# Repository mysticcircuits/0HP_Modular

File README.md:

# 0HP_Modular
A collection of small circuit boards meant to save space in a Eurorack modular synthesizer.

However they can be adapted and used in all kinds of scenarios, including other formats.

All of the 0HPs have a video build guide where I walk you through the build in real time.  These modules are ideal for DIY beginners and I wanted to make things easier for beginners to follow along like a Bob Ross video.  For the relevant videos, look at the links below:

0HP 0ttenuator: https://youtu.be/Et-Cd0Tk92Y

0HP Butt0n: https://youtu.be/Q1uErexXjrM

0HP Blinkus: https://youtu.be/KXeKGlNDjDo

0HP OR Gate: https://youtu.be/0qNCt1tknoM

0HP AND Gate: https://youtu.be/TZeJ5ZJfBpM

0HP Vactrol Modules: https://youtu.be/1y4UL7ndCgU

0HP EYEtenuator: https://youtu.be/DLzy-zN2tSA

0HP Filter: https://youtu.be/64bybnugtrU

0HP Envelope: https://youtu.be/DnMquwOY_Zk

If you are new to soldering, here is a guide I made going over the basics: https://www.youtube.com/watch?v=Z_U6xBCo2K4

Please note that these files are shared under the Creative Commons Attribution-NonCommercial 3.0 United States (CC BY-NC 3.0 US) licence, details of which can be found here:

https://creativecommons.org/licenses/by-nc/3.0/us/

This licence prohibits using these designs for commercial use.  Feel free to make circuit boards for yourself but we ask that you not sell them.  If you are interested in purchasing either a circuit board, panel or kit you can go to our website or visit one of our retailers.

http://www.mysticcircuits.com/

https://www.thonk.co.uk/shop/mystic-circuits-0hp-modular-pcbs/

Enjoy the designs <33

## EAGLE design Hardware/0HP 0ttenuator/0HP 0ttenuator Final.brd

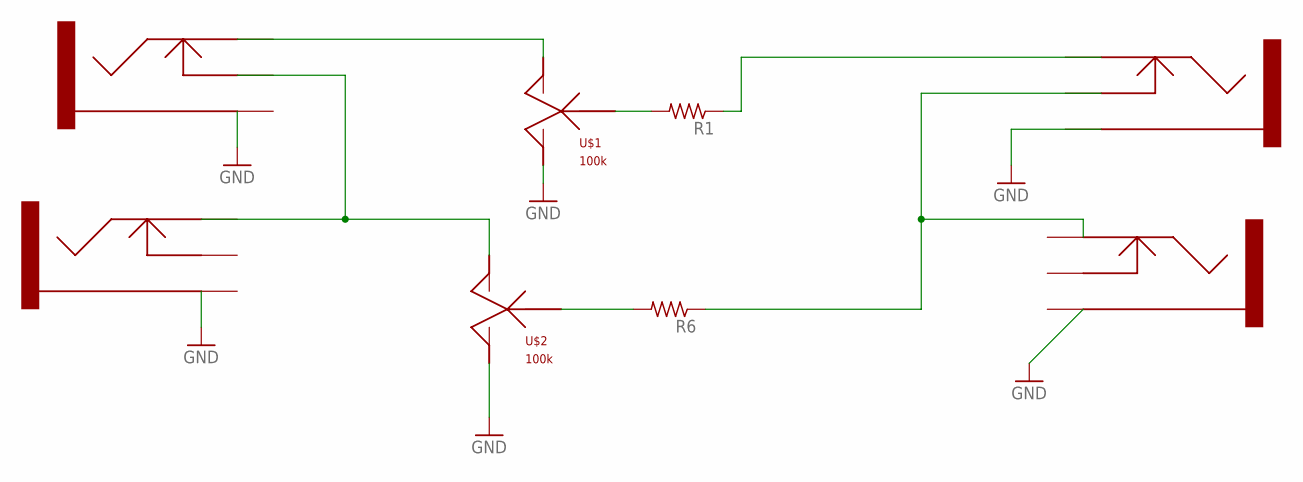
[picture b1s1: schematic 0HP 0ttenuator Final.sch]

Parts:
CV1, CV2: 3.5MMJACK; 3.5MMPHONEJACK
IN: 3.5MMJACK; 3.5MMPHONEJACK
OUT: 3.5MMJACK; 3.5MMPHONEJACK
R1, R6: R-US_0207/10; 0207/10
U$1, U$2: 100k; ALPHAPOT_BOARDMOUNT

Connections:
GND: CV1.SLEEVE, CV2.SLEEVE, IN.SLEEVE, OUT.SLEEVE, U$1.RIGHT, U$2.RIGHT
unnamed: CV2.TIP, U$1.LEFT
unnamed: R1.2, U$1.MID
unnamed: CV1.TIP, CV2.SWITCH, U$2.LEFT
unnamed: OUT.TIP, R1.1
unnamed: IN.TIP, OUT.SWITCH, R6.1
unnamed: R6.2, U$2.MID

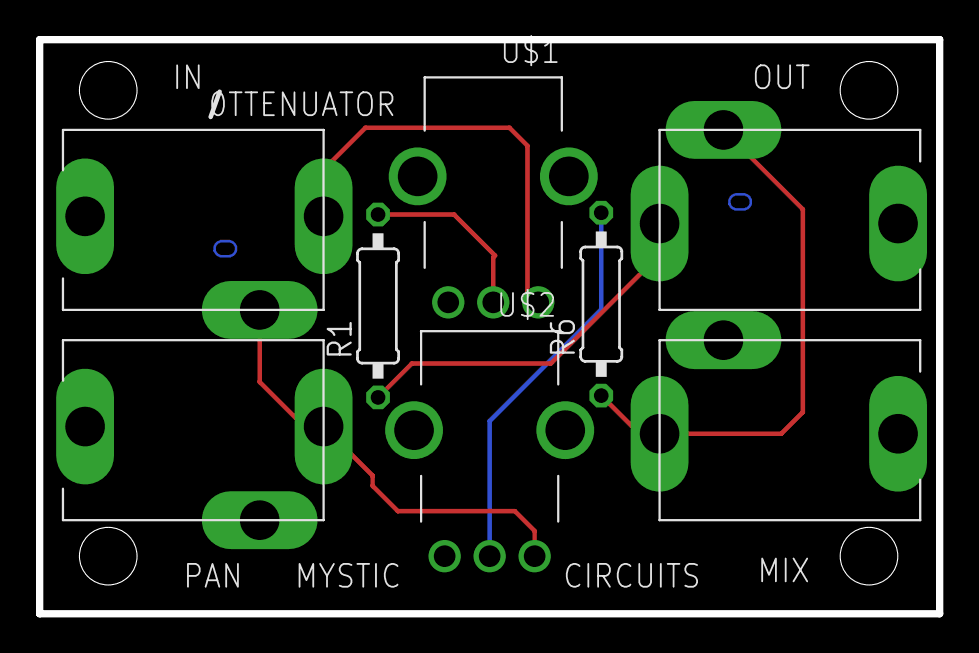
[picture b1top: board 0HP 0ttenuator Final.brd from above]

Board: 2 copper layers, 50.0 x 31.9 mm, 8 parts (0 on the bottom side), 7 nets.

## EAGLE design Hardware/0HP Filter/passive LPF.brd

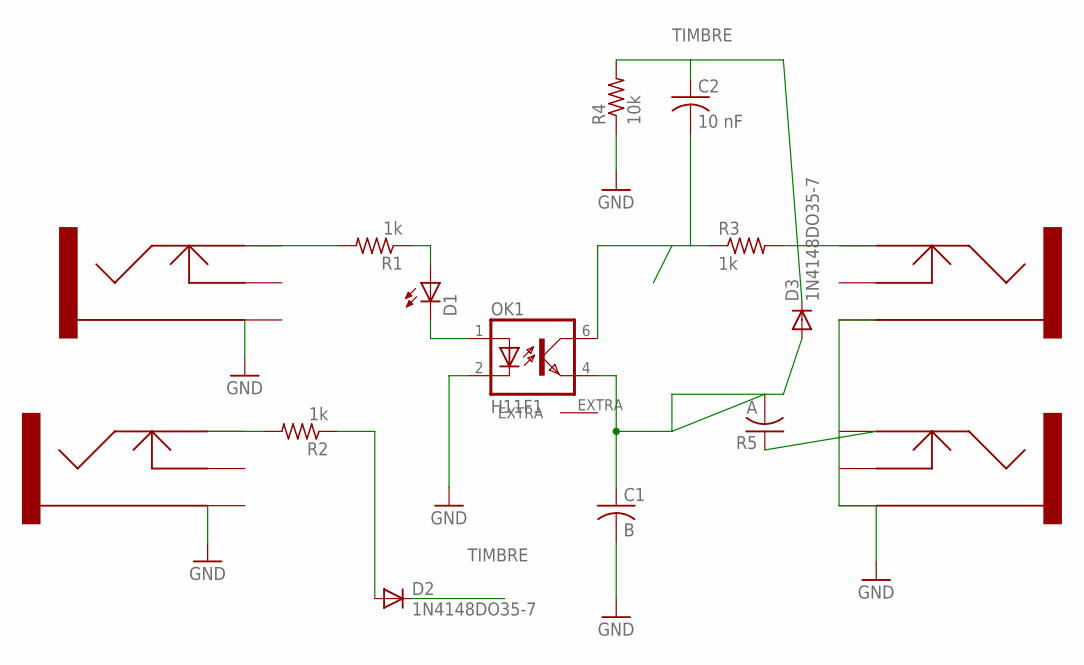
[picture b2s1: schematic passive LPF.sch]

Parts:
C1: B; C050-025X075
C2: 10 nF; C025-024X044
CV1, CV2: 3.5MMJACK; 3.5MMPHONEJACK
D1: LED3MM
D2, D3: 1N4148DO35-7; DO35-7
IN: 3.5MMJACK; 3.5MMPHONEJACK
OK1: H11F1; DIL05
OUT: 3.5MMJACK; 3.5MMPHONEJACK
R1, R2, R3: 1k; 0207/2V
R4: 10k; 0207/2V
R5: A; C050-025X075

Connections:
GND: C1.2, CV1.SLEEVE, CV2.SLEEVE, IN.SLEEVE, OK1.2 (C), OUT.SLEEVE, R4.1
unnamed: CV2.TIP, R1.2
unnamed: D1.A, R1.1
unnamed: D1.K (C), OK1.1 (A)
unnamed: CV1.TIP, R2.2
unnamed: D2.A, R2.1
unnamed: C1.1, D3.A, OK1.4 (EMIT), R5.2
unnamed: C2.2, OK1.6 (COL), R3.1
unnamed: IN.TIP, R5.1
unnamed: OUT.TIP, R3.2
TIMBRE: C2.1, D2.C, D3.C, R4.2

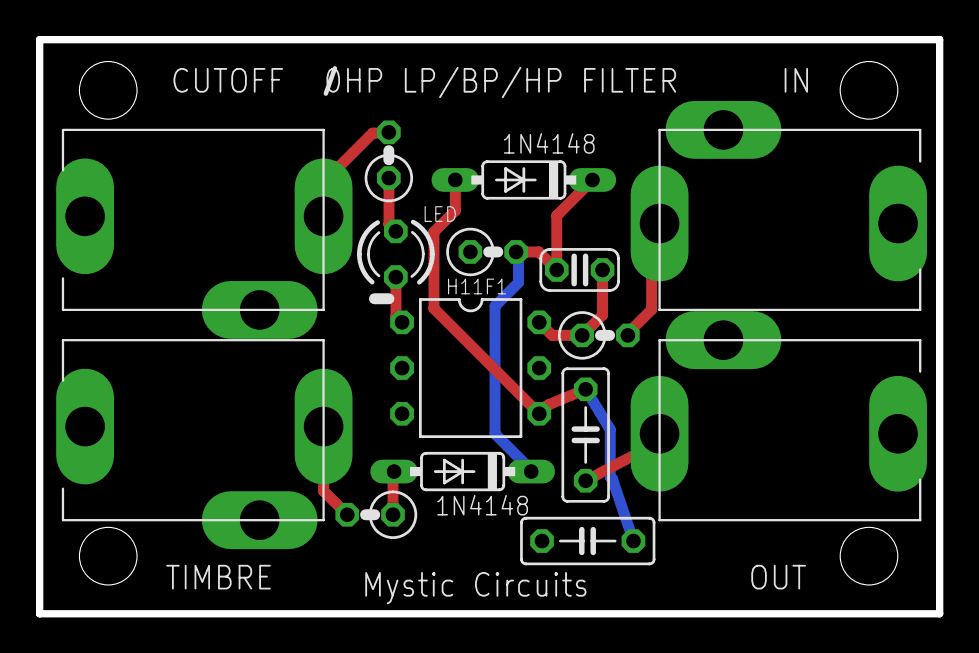
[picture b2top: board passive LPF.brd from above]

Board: 2 copper layers, 50.0 x 31.9 mm, 15 parts (0 on the bottom side), 11 nets.

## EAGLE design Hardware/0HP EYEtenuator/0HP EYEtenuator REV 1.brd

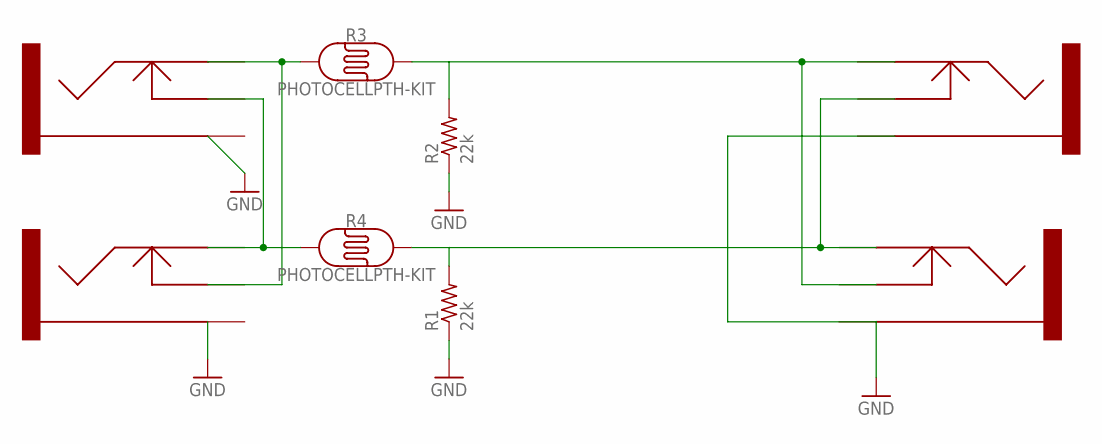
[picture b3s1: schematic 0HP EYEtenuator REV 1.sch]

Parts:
CV1, CV2: 3.5MMJACK; 3.5MMPHONEJACK
IN: 3.5MMJACK; 3.5MMPHONEJACK
OUT: 3.5MMJACK; 3.5MMPHONEJACK
R1, R2: 22k; 0207/2V
R3, R4: PHOTOCELLPTH-KIT; PHOTOCELL-KIT

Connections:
GND: CV1.SLEEVE, CV2.SLEEVE, IN.SLEEVE, OUT.SLEEVE, R1.1, R2.1
unnamed: IN.TIP, OUT.SWITCH, R1.2, R4.2
unnamed: CV1.SWITCH, CV2.TIP, R3.1
unnamed: CV1.TIP, CV2.SWITCH, R4.1
unnamed: IN.SWITCH, OUT.TIP, R2.2, R3.2

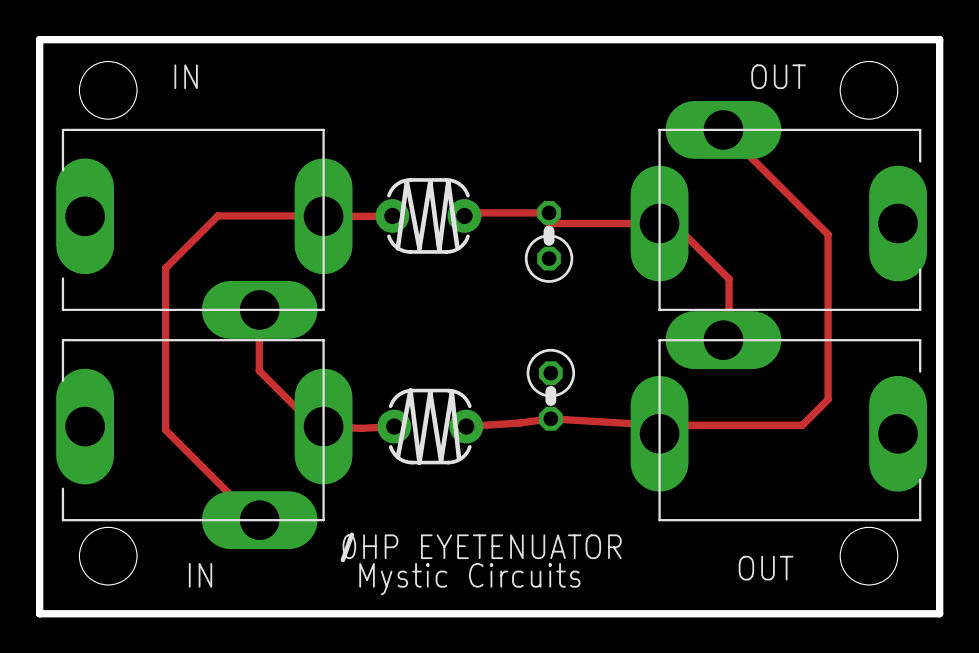
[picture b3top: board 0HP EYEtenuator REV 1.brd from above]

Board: 2 copper layers, 50.0 x 31.9 mm, 8 parts (0 on the bottom side), 5 nets.

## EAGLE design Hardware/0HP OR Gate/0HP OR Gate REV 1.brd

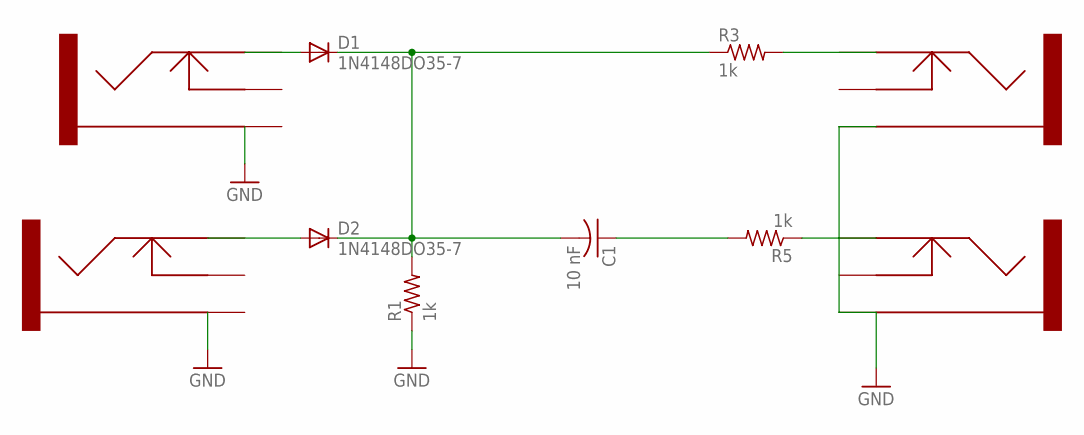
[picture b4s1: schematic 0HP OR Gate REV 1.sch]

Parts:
C1: 10 nF; C025-024X044
CV1, CV2: 3.5MMJACK; 3.5MMPHONEJACK
D1, D2: 1N4148DO35-7; DO35-7
IN: 3.5MMJACK; 3.5MMPHONEJACK
OUT: 3.5MMJACK; 3.5MMPHONEJACK
R1, R3, R5: 1k; 0207/2V

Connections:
GND: CV1.SLEEVE, CV2.SLEEVE, IN.SLEEVE, OUT.SLEEVE, R1.1
unnamed: CV2.TIP, D1.A
unnamed: CV1.TIP, D2.A
unnamed: C1.1, R5.2
unnamed: C1.2, D1.C, D2.C, R1.2, R3.1
unnamed: IN.TIP, R5.1
unnamed: OUT.TIP, R3.2

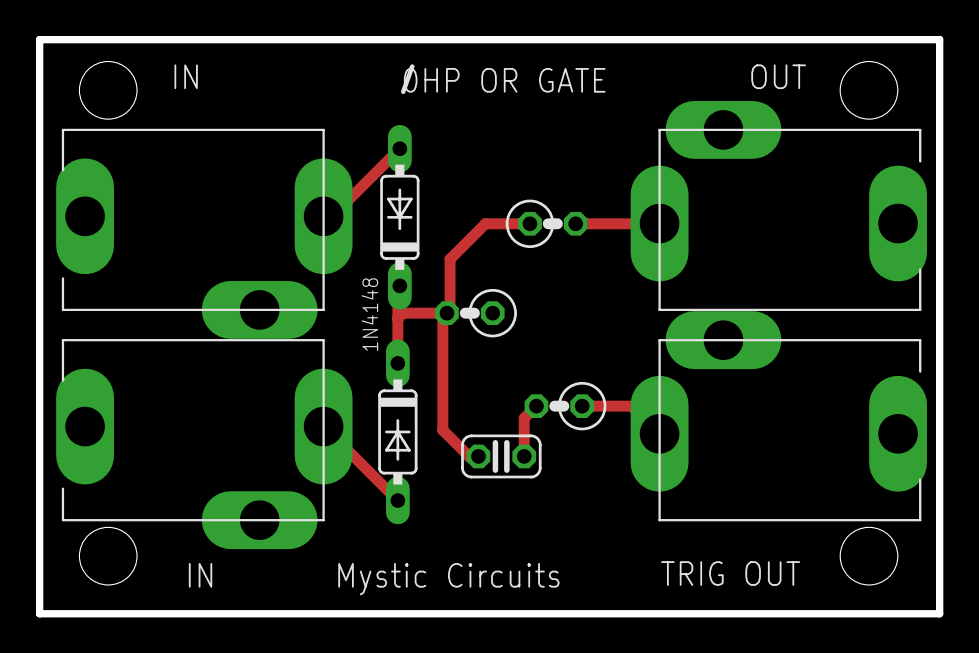
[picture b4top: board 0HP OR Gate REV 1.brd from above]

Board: 2 copper layers, 50.0 x 31.9 mm, 10 parts (0 on the bottom side), 7 nets.

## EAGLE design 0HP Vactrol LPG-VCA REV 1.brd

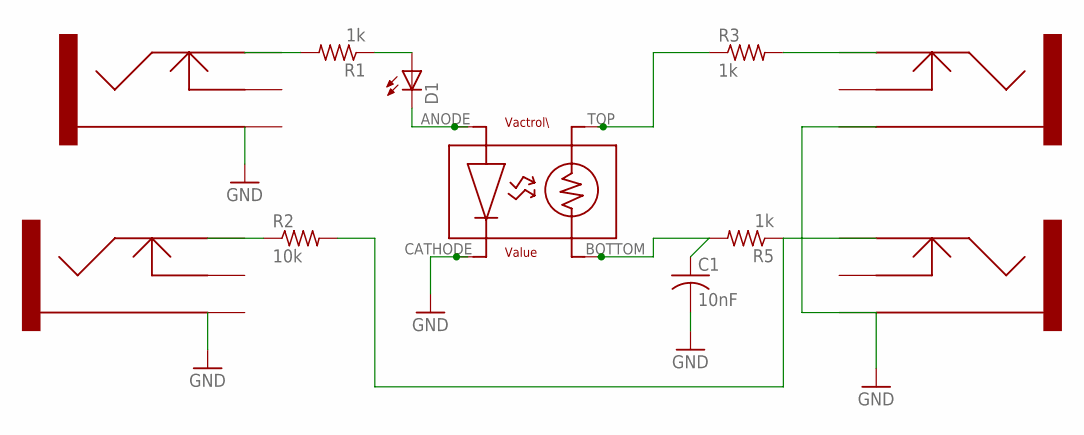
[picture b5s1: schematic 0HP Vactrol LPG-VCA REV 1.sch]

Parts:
C1: 10nF; C025-024X044
CV1, CV2: 3.5MMJACK; 3.5MMPHONEJACK
D1: LED3MM
IN: 3.5MMJACK; 3.5MMPHONEJACK
OUT: 3.5MMJACK; 3.5MMPHONEJACK
R1, R3, R5: 1k; 0207/2V
R2: 10k; 0207/2V
U$1: VACTROL

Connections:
GND: C1.2, CV1.SLEEVE, CV2.SLEEVE, IN.SLEEVE, OUT.SLEEVE, U$1.CATHODE
unnamed: CV2.TIP, R1.2
unnamed: D1.A, R1.1
unnamed: CV1.TIP, R2.1
unnamed: C1.1, R5.2, U$1.BOTTOM
unnamed: D1.K (C), U$1.ANODE
unnamed: R3.1, U$1.TOP
unnamed: IN.TIP, R2.2, R5.1
unnamed: OUT.TIP, R3.2

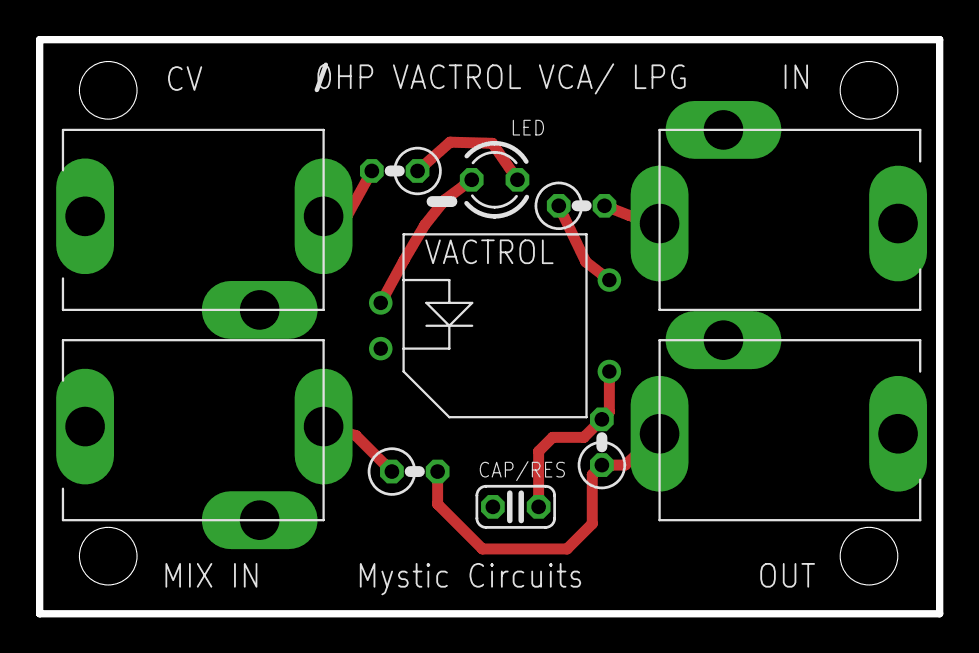
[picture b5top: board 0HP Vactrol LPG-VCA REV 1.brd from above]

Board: 2 copper layers, 50.0 x 31.9 mm, 11 parts (0 on the bottom side), 9 nets.

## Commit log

2018-04-26 Create sdfdf
2018-04-26 Rename 0HP Vactrol LPG-VCA REV 1.brd to Hardware/0HP Vactrol LPG-VCA REV 1.brd
2018-04-26 Rename 0HP Vactrol LPG-VCA REV 1.sch to Hardware/0HP Vactrol LPG-VCA/0HP Vactrol LPG-VCA REV 1.sch
2018-04-26 Rename Hardware/0HP Vactrol LPG-VCA REV 1.brd to Hardware/0HP Vactrol LPG-VCA/0HP Vactrol LPG-VCA REV 1.brd
2018-04-26 Create fdfd
2018-04-26 Create kldhfkjdf
2018-04-26 Create lkdfljf
2019-11-28 Create kdjfdkfds
2019-11-28 Create dlkfjdlfkjd
2019-11-28 Create kjkjhkj
2020-04-24 Create sldkjfkj
2023-07-06 Create ddsssdds
2023-07-06 Create readme
    A place to put more notes on the new circuit board files.
2023-07-06 File to put notes on AND Gate
2023-07-06 Create deleteme
2023-07-06 Rename deleteme to deleteme
2023-07-06 Rename readme to readme

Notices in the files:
parts and their libraries:
SparkFun-Sensors: Licensing: Creative Commons ShareAlike 4.0 International - https://creativecommons.org/licenses/by-sa/4.0
